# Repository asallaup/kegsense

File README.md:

# Sallaup KegSense

Keg weight/level monitoring for a keezer, by **Sallaup Electronics**.

Each keg sits on a load cell. A per-keg board reads the weight and sends
it over a wired connection to a central unit, which streams each keg's
brew name + weight out to a small OLED mounted right at that keg's own
tap (its own tiny MCU drives the display, right where you're pouring
from) and mirrors the same view to a web dashboard you can check
remotely — so you know how much beer is left without opening the lid.

## System overview

```
 Keg 1  --RJ11-->  |                |
 Keg 2  --RJ11-->  |     KegHub     |  --RJ45-->  KegStation
 Keg 3  --RJ11-->  |   (passive     |             (Raspberry Pi,
 Keg 4  --RJ11-->  |    wiring      |              web dashboard)
 Keg 5  --RJ11-->  |    panel)      |                   |
                    |                |                   v
                                              KegDisplay chain (OLED +
                                              Trinket M0 per tap, daisy-
                                              chained tap to tap)
```

Each keg's board is a **KegSensor** module (HX711 + 4 half-bridge strain
gauge sensors + RJ11 out). No Wi-Fi or radio anywhere inside or on the
keezer itself — everything in there is wired; KegStation, which sits
outside the keezer, is the only part with Wi-Fi (for the dashboard).

## Status

- 🚧 **KegSensor** (per-keg module) — **draft design**, still likely to
  change. Schematic + PCB routed and DRC-clean, 3D-printable case
  designed and validated, fab-ready Gerbers generated — but none of it
  has been physically built, and it hasn't been ordered/printed yet.
  Treat as a working draft, not a locked design, until it's been through
  a real build.
- 🚧 **KegHub** (in-keezer passive wiring panel) — wiring design
  (RJ11/RJ45 pin conventions, parts list) documented; physical build not
  started.
- 🚧 **KegStation** (central unit) — architecture decisions documented
  (platform, Wi-Fi provisioning, update mechanism, KegSensor-interfacing
  daemon language); no hardware or software built yet.
- 🚧 **Keg platform** (load cell mounting) — one part done: a derived,
  validated OpenSCAD load cell holder. Top/bottom mounting plates around
  it not designed yet.

## Repo layout

- [`hardware/kegsensor/`](hardware/kegsensor/) — KegSensor: per-keg
  sensor wiring (RJ11 pin conventions, parts list), KiCad schematic/PCB
  project, 3D-printable case (OpenSCAD), fab-ready Gerbers, and the load
  cell platform holder. See its own README(s) for details, known
  assumptions to verify against real hardware, and how to regenerate
  everything.
- [`hardware/keghub/`](hardware/keghub/) — KegHub: the in-keezer passive
  wiring panel design (RJ45 pin conventions, parts list, bench-test
  checklist).
- [`hardware/kegstation/`](hardware/kegstation/) — KegStation (central
  unit) planning doc: decisions made so far and what's still open.
- [`hardware/kegdisplay/`](hardware/kegdisplay/) — KegDisplay (per-keg
  tap indicator) planning doc: a small OLED + its own Trinket M0 MCU per
  tap, daisy-chained back to KegStation, each tap showing its own keg's
  brew name + weight directly.

## Before ordering/building anything

Both `hardware/kegsensor/README.md` and `hardware/kegsensor/wiring.md`
flag specific assumptions (HX711 module pin order, sensor diagonal
wiring) that need confirming against the actual parts once they're in
hand — cheap to fix now, annoying after boards are fabricated.

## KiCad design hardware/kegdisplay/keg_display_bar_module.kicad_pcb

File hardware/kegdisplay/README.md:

# KegDisplay — Sallaup Electronics

Part of the **Sallaup KegSense** keg-monitoring system, made by
**Sallaup Electronics**.

**KegDisplay** is the per-keg status indicator: a vertical WS2812 LED
bar in its own enclosure, mounted on the collar's side at each tap,
showing that keg's remaining % as a fill-level bar (more LEDs lit from
the bottom = more left — same read as a fuel gauge). No per-tap MCU —
**KegStation** (the central Raspberry Pi — see
[`../kegstation/`](../kegstation/)) drives the whole chain directly.
An off-the-shelf WS2812 strip is glued or screwed to the front of a
small custom PCB inside the enclosure, which gives it a rigid mount and
carries both chain connectors (see the revision note below for how this
settled). Brew-name display is a separate, experimental add-on — see
[`../kegtag/`](../kegtag/).

This is a planning doc — no hardware or software has been built yet.
Captures decisions made so far so they aren't lost before implementation
starts (see [`../kegsensor/wiring.md`](../kegsensor/wiring.md) and
[`../keghub/README.md`](../keghub/README.md) for the equivalent docs
that preceded the KegSensor module).

**Revision note**: this design has gone through several full rewrites,
kept in git history rather than deleted outright:
1. Originally an Arduino Nano + MAX485 board per tap, daisy-chained over
   RS-485 with a custom chain-position auto-addressing scheme.
2. Then a bare OLED module per tap wired star-topology through a
   TCA9548A I2C multiplexer at KegStation, dropping the Nano entirely.
3. Then, realizing an OLED at every tap was itself more display than the
   job needed, the per-tap hardware shrank further to just a status LED
   + a pushbutton, with the actual detailed information (brew name,
   weight) moved to a screen at KegStation instead.
4. **This version**: brings the OLED back, but on a much smaller MCU
   with its own onboard I2C - each tap's OLED shows its own brew name +
   weight directly, all the time, no button/KegStation-touchscreen
   detail view needed. The Nano-sized objection that killed revision 1
   doesn't apply this time; the shared-I2C-address conflict that killed
   the mux approach in revision 2 doesn't apply either (each tap's OLED
   is on its *own* MCU's I2C bus, not a bus shared across taps). The MCU
   choice within this revision itself went through several rounds:
   Adafruit Trinket M0 (real hardware I2C, easy USB/Arduino flashing,
   but ~$5-6/unit) -> Seeeduino XIAO SAMD21 (same capability, smaller
   board, similar cost) -> ATtiny10 (tiny and ~$0.30, but no hardware
   I2C/UART and needs a TPI programmer) -> CH32V003 (cheapest of all,
   ~$0.10-0.15, real hardware I2C, but RISC-V + WCH-LinkE is a bigger
   toolchain departure than anything else in this project) ->
   **ATtiny1614 in SOIC-14**, the settled choice: real hardware I2C,
   16KB flash/2KB RAM (enough for real OLED text, unlike ATtiny10's
   1KB), ~$0.60-1.20/unit (far cheaper than Trinket M0/XIAO, only a
   modest premium over CH32V003), programmed over UPDI (simpler than
   ATtiny10's TPI - a USB-serial adapter + one resistor is enough), and
   SOIC-14 is still hand-solderable (unlike QFN packages, which need
   reflow/hot air).
5. **This version**: dropped the OLED+MCU entirely. The real physical
   constraints at the mounting location (~100mm between taps, ~30mm max
   height) kept defeating every attempt to fit the ATtiny1614+OLED+
   connector assembly — landscape reorientation, connector swaps
   (KK-254 vs RJ14 vs audio jack), aggressive layout compaction all hit
   walls, most fundamentally that any locking/panel-mount connector's
   physical plug needs ~12-20mm of depth, which doesn't fit in the
   ~12mm gap left between taps once a board of any reasonable size is
   in place. Back to a WS2812 LED chain (first explored in revision 3),
   but as a 10-LED bar graph per tap instead of a single status LED,
   and with KegStation driving the chain directly — no per-tap
   MCU/logic at all, sidestepping the space problem instead of
   continuing to fight it.
6. **This version**: switched from a horizontal custom-PCB LED bar to a
   **vertical off-the-shelf WS2812B LED strip** mounted on the collar's
   side (~50mm width x ~130mm height available there - a much bigger
   budget than the ~100x30mm the horizontal layout was fighting for).
   Two wins at once: (1) a commercial strip at 140-200 LEDs/m gives
   18-26 LEDs over that length, cut to whatever length is wanted, so
   there's no custom PCB to design/fab at all - just a cut strip with a
   few wires soldered on at each end; (2) a vertical fill-level bar
   reads more intuitively than a horizontal one (same mental model as a
   fuel gauge or thermometer).
7. **This version**: brought a custom PCB back after all — not because
   the vertical layout was wrong, but to solve two things a bare
   commercial strip couldn't: a rigid mounting surface inside the box,
   and a way to get *both* chain connectors onto the box's bottom edge
   (see "connectors on left/right" below — both need to end up at the
   bottom, and a floppy 3-wire strip has no natural way to route a
   return path back down). Individual WS2812B LEDs are placed directly
   on a 2-layer PCB instead: front layer carries the LED chain bottom to
   top; after the top LED, a via drops the single DATA_OUT signal to the
   back layer, which routes it back down to the bottom-right connector.
   VCC/GND don't need this detour — they're shared rails running the
   full board height on the front layer, tapped directly by both
   connectors.
8. **This version**: swapped the 23 individually-placed LED footprints
   for an off-the-shelf WS2812 strip, glued or screwed to the front of
   the custom PCB. The PCB still solves the same two problems revision 7
   introduced it for (rigid mounting surface, both connectors on the
   bottom edge) — that didn't change. What changed: hand-laying out 23
   LED footprints/nets was more work than buying an assembled strip and
   mounting it. The PCB's job shrinks to rigid backer + both connectors
   + a soldered-wire path (the strip's own DIN/DOUT leads soldered to
   pads) instead of continuous copper running through 23 LED footprints.
   Nothing below reflects revision 7's individual-LED approach.

## Decisions so far

- **Per tap: an off-the-shelf WS2812 LED strip, glued or screwed to the
  front of a custom 2-layer PCB**, mounted vertically inside an
  enclosure on the collar's side. No per-tap MCU — KegStation lights
  however many LEDs correspond to the keg's remaining % as a bottom-up
  fill bar. Same chain-position addressing as every earlier revision —
  purely protocol-level, no firmware/logic at the tap.
- **Topology: daisy chain, 3 conductors (+5V, GND, WS2812 data)**,
  same as every earlier revision.
- **Power: 5V**, matching the Pi's logic level, same as every earlier
  revision — but sourced from its own dedicated supply injected into
  the chain, not drawn through the Pi itself (see
  [`../kegstation/README.md`](../kegstation/README.md) for why: LED
  current draw exceeds what the Pi's own PSU/GPIO can safely provide).
- **Mounting location: collar's right side, vertical**, not the tap
  face — ~50mm width x ~130mm height available there. Confirmed against
  the real keezer, not guessed: tap spacing ~10cm apart horizontally
  (real photo, 5 taps through a single wood plank, plus a direct
  measurement), collar board height 13cm (matches the ~130mm figure
  almost exactly), and the board is confirmed finished wood (despite
  looking unfinished in the photo) — the earlier reasoning against
  drilling a blind bore for cable routing (a visible mistake in
  installed, finished wood, with no way to redo it) holds as originally
  reasoned. Board thickness is the only dimension still unmeasured (see
  Still Open).
- **Housed in a rectangular enclosure** — protects the PCB and gives the
  LEDs a diffuser window instead of exposed dots. Box footprint sized to
  the ~50x130mm mounting budget above.
- **Both connectors live on the box's bottom edge, one on the left, one
  on the right, each with a short wire pigtail to the next tap's box** —
  not top/bottom of the box, even though the PCB inside runs vertically.
  Taps sit ~10cm apart *horizontally* along the collar, so the
  daisy-chain cable between one tap's box and the next needs to run
  sideways; bottom-left/bottom-right connector placement matches that
  real cable path instead of forcing an awkward top-to-bottom-then-across
  route.
- **PCB signal routing**: left connector (chain in) feeds pads at the
  strip's bottom (DIN) end via soldered wire leads. The strip itself
  carries data up its own length front-side; its DOUT lead at the top
  end solders to a pad, where a via drops DATA_OUT to the back layer,
  routing it straight back down to the right connector (chain out) —
  same detour concept as revision 7, now via a soldered wire+pad instead
  of continuous LED-to-LED copper. VCC/GND: the strip's own power leads
  solder to pads tied to shared rails on the front layer spanning the
  full board height, tapped directly by both connectors.
- **Mounting method (glue vs. screw) depends on which strip is
  sourced** — a flexible, adhesive-backed strip (the common type) only
  supports gluing; a rigid-PCB or aluminum-channel strip variant would
  support screws if one is sourced instead. Not decided (see Still
  Open).
- **PCB laid out and DRC-clean, board size settled: 34x132mm**, offset
  from the origin (x: 9.5-43.5mm, y: -2-130mm) — resized/shifted in the
  KiCad GUI from the original 50x130mm placeholder and confirmed as the
  right size. `generate_bar_schematic.py` / `generate_bar_pcb.py` in
  this directory build this board, kept in sync with that GUI edit.
  Which specific off-the-shelf strip to buy is still open (see Still
  Open) but must now fit this board size, not the other way around.
  J1/J2 still near the bottom, outward-
  facing (cable exits sideways), nudged off strict edge-flush/shared-Y
  placement in the GUI to clear each other's and MH2's courtyards after
  the resize. R1/C1 between them (unchanged). TP1-3 (strip's bottom
  GND/VCC/DIN leads) and TP4-6 (strip's top GND/VCC/DOUT leads) remain a
  tight 4mm-pitch cluster of hand-solder test points, replacing the 23
  LED footprints. Mounting holes MH1/MH2 both moved to the board's
  horizontal center in the GUI. ERC/DRC clean aside from known-benign
  warnings (`lib_footprint_mismatch` from UUID regeneration;
  `silk_over_copper` from the connectors' own default pin-1 silkscreen;
  `unconnected_items` since, like every earlier revision's generator
  script, this places components and assigns nets but does **not** emit
  copper traces/vias — it validates physical fit and clearance, not
  routing completeness; the DATA_OUT via + back-layer return trace is a
  routing detail for real layout, not modeled here).

## Superseded (revision 7, individual LEDs on PCB) — kept for reference

- **Per tap: 23x WS2812B-2020 (2.0x2.0mm) LEDs at 5mm pitch (200 LEDs/m)
  soldered directly onto the custom 2-layer PCB** — the smaller 2020
  package (vs. revision 5's 3.5x3.5mm Mini) gave comfortable clearance
  at this tight pitch. Superseded by revision 8's off-the-shelf strip
  glued/screwed to the same PCB — hand-laying out 23 individual LED
  footprints/nets was more generator-script work than buying an
  assembled strip; the PCB's role (rigid mount, both connectors on the
  bottom edge) carries forward unchanged.
- **PCB signal routing (individual-LED version)**: left connector fed
  the bottom LED's DIN directly; data climbed LED to LED on the front
  layer to the top LED's DOUT, where a via dropped DATA_OUT to the back
  layer, routed back down to the right connector. Same detour concept
  revision 8 keeps, just via continuous LED-to-LED copper instead of a
  strip's own leads soldered to pads.
- **PCB laid out and DRC-clean for this construction**:
  `generate_bar_schematic.py` / `generate_bar_pcb.py` in this directory
  build *this* (now superseded) board — 23 LEDs at 5mm pitch, board
  50x130mm, J1 bottom-left / J2 bottom-right both facing outward
  (JST-PH 3-pin horizontal, same footprint/angles as revision 5), R1/C1
  between them. ERC/DRC clean aside from known-benign warnings
  (`power_pin_not_driven` on VCC/GND — same accepted quirk as every
  earlier revision's schematic; `lib_footprint_mismatch` from UUID
  regeneration; `silk_over_copper` from the connectors' own default
  pin-1 silkscreen crossing their own pads). **Not yet regenerated for
  revision 8** — these scripts still model the individual-LED
  construction, not the strip-on-backer-PCB one (see Still Open).

## Superseded (revision 6, off-the-shelf strip) — kept for reference

- **Per tap: a commercial WS2812B LED strip (140-200 LEDs/m), cut to
  length.** No custom PCB. Superseded by revision 7's custom PCB, needed
  to give the strip a rigid mounting surface and to route a return path
  to both bottom connectors (see revision note above) — otherwise the
  core idea (vertical fill bar, ~50x130mm collar-side mounting, no
  per-tap MCU) carries forward unchanged.
- **Topology detail specific to a cut strip**: 3 pads at each end, a
  short pigtail soldered on at each end carrying them to a chain
  connector. Moot once LEDs are placed directly on a PCB instead.

## Superseded (revision 5, custom PCB LED bar) — kept for reference

The horizontal custom-PCB version (generate_schematic.py/generate_pcb.py
in this directory) went through extensive layout work — 10 LEDs down to
5, connector swaps, edge-flush J1/J2 for case-wall cutout access — all
now moot since revision 6 uses a cut length of commercial strip instead
of a custom board. Kept as-is in this directory rather than deleted;
treat as historical, not a current target to keep building against.

## Superseded (revision 4, ATtiny1614+OLED) — kept for reference

- **Per tap: one ATtiny1614 (SOIC-14) + one 0.91" SSD1306 I2C OLED.** The
  ATtiny1614 is its own I2C master for its own OLED — no shared bus, no
  address conflict, no mux (that was revision 2's problem, and it simply
  doesn't arise here since each tap's I2C bus is private to that tap).
  No button, no resistor ladder, no KegStation-side ADC — the OLED just
  always shows its own keg's brew name + weight. See the revision note
  above for the full MCU comparison (Trinket M0/XIAO/ATtiny10/CH32V003)
  that led here.
- **Development workflow: Arduino IDE + megaTinyCore, prototype on a
  SOIC-to-DIP adapter, flash over UPDI, keep a UPDI header on the final
  board.** Concretely:
  1. Write firmware as a normal Arduino sketch (megaTinyCore adds
     ATtiny1614 as a board option, `Wire.h` works for I2C).
  2. Prototype on a breadboard by soldering the chip onto a cheap
     SOIC-14-to-DIP adapter board first, rather than committing straight
     to a custom PCB.
  3. Flash via **SerialUPDI** — a plain USB-to-serial adapter plus one
     resistor between its TX/RX lines, wired to the chip's UPDI pin.
     megaTinyCore supports this directly as an Arduino IDE upload
     method, so it's still just "hit Upload."
  4. Once firmware is solid, solder a chip onto the real per-tap PCB,
     which includes its own **3-pin UPDI header (UPDI/VCC/GND)** so it
     can be reflashed in place later (fixing a bug or tweaking the OLED
     layout after it's already mounted at the tap) without desoldering.
  5. **Field reflashing: temporary cable from KegStation's own UART pins
     to J4, one tap at a time** — a Pi's UART (TX/RX) can run SerialUPDI
     directly, so KegStation itself is the programmer, no separate
     laptop/USB adapter needed. Not a permanent connection (UPDI is
     point-to-point; it can't ride the shared chain bus without hitting
     every tap's chip at once) — walk up to the tap, plug in, flash,
     unplug. J4 stays inside the case (no dedicated access port needed
     in the lid/body — see Still Open) since this is infrequent enough
     that opening the case is an acceptable cost.
  6. **Possible future upgrade, not implemented now**: a bootloader that
     receives firmware over the chain itself (via J1, reusing the same
     "consume my chunk, relay the rest" addressing idea as the brew-data
     relay), removing the need to physically visit a tap at all for
     routine updates. J4/UPDI would still be needed for a blank chip's
     very first flash either way. Deliberately deferred — not worth the
     bootloader complexity until the rest of the system is proven out.
- **Chain addressing: still positional, like the WS2812 version, but now
  relayed by firmware instead of being protocol-free.** KegStation
  streams all 5 kegs' data down the chain in tap order; each ATtiny1614
  reads its own chunk off its "chain in" pin (a bit-banged serial RX),
  keeps that chunk for its own OLED, and relays everything after it out
  its "chain out" pin (bit-banged serial TX) to the next tap. No
  per-tap address to configure, same principle as the LED chain, just
  carrying real data (text) instead of raw color bits.
  - **Pin budget**: ATtiny1614 (SOIC-14) has 14 pins total: VDD, GND,
    UPDI (shared with reset, freed up by the UPDI header above), and 11
    GPIO. 2 go to hardware I2C (SDA/SCL, to the OLED), 2 to chain
    in/chain out, leaving several spare — a much more comfortable
    budget than Trinket M0's 5 broken-out GPIO.
- **Topology: daisy chain**, one cable hopping tap to tap, same as the
  WS2812 version and for the same reason — the chain-position addressing
  scheme requires it.
  - **3 conductors used: +5V, GND, chain data** (one direction only —
    KegStation "down" through the chain; no need for a return path,
    since each tap only needs to receive, not report back). 2 jacks per
    tap (IN from upstream, OUT to downstream), **Molex KK-254 (4-pin,
    2.54mm pitch)** — not RJ14 like KegSensor's jack, switched for board
    size (KK-254's courtyard is ~1/3 RJ14's) while keeping a real
    locking latch, unlike JST-PH (used only for the short internal OLED
    cable, where no latch is needed). 4th contact left unused/spare.
  - **Same known IN/OUT-swap fragility as the WS2812 version, re-accepted
    for the same reason**: chain-in and chain-out are different pins on
    the Trinket, not symmetric, so a swapped cable breaks that tap and
    everything downstream of it. Worth keying/labeling the jacks clearly
    at install time.
  - **Chain fragility**: a disconnected or dead tap breaks every tap
    downstream of it, same as any physical daisy chain — already
    discussed and accepted in the WS2812 revision, still true here.
- **Power: 5V** on the shared rail, matching the Pi's own 5V — the OLED
  module runs fine off 5V directly (most SSD1306 breakouts have their
  own onboard 3.3V regulator). ATtiny1614's own VDD range/regulation
  need still needs confirming (see Still Open) - it may need a small
  local 3.3V regulator on the per-tap board, unlike Trinket M0 which
  handled that internally.
- **OLED-to-board cable: 4-pin JST-PH (2mm pitch).** The lid-to-body run
  is under 2cm, short enough that a compact connector fits better than
  a pin header — hand-solderable, unlike the finer 1mm-pitch JST-SH
  alternative.
- **Mounting location: outside the keezer** — the OLED/ATtiny1614
  assembly sits on the tap's own exterior face, same reasoning as every
  earlier revision: no part of the wiring needs to enter the cold zone.
- **Mechanical split: main board inside the case body, OLED mounted on
  the case lid, connected between them by a short wire harness** (not a
  single rigid board carrying both) - decided when starting the case/lid
  design, still in progress (see Still Open). The OLED's 4-pin header
  (VCC/GND/SCL/SDA) on the main board is exactly this cable's connection
  point, not a directly-soldered display.
- **Physical cable routing: hidden along the collar's exterior, under a
  paintable plastic cord cover** — not routed through the collar's
  interior cavity (both ends are already outside, so dipping into the
  cold zone would be pure downside), and not bored through the solid
  wood either (the collar here is already built and finished — a long
  blind bore through installed wood risks a visible drilling mistake
  with no way to redo it, unlike drilling before assembly). Cable runs
  along an inconspicuous exterior seam (e.g. where the collar meets the
  freezer body) and is covered by an off-the-shelf paintable plastic
  cord cover, painted to match — reads as a deliberate trim detail
  instead of an exposed wire.
- **Not yet built or prototyped** — this whole design came out of
  conversation, not a physical test yet. Same "verify against real
  hardware before calling it done" standard as everything else in this
  project.

## Still open

- **Which off-the-shelf strip to source** — not chosen. Board size
  (34x132mm) is now settled, so this is a fit-to-board search, not an
  open-ended one: needs a strip whose usable length fits the ~132mm
  board height, with end-lead spacing compatible with the TP1-3/TP4-6
  hand-solder clusters (revisit their exact positions in
  `generate_bar_pcb.py` once a strip is picked, if its real lead spacing
  differs from the current placeholder). Also determines whether glue or
  screws are possible (see "Mounting method" above — needs a rigid-PCB
  or aluminum-channel strip for screw-mounting; a standard flexible
  adhesive-backed strip only glues).
- **Enclosure: first-draft 3D-printable case modeled, NOT verified
  against real hardware yet.** `case_bar.scad` /
  `generate_case_bar.sh` (this directory) build two parts: `base`
  (solid wall — no window, side walls with left/right cutouts for
  J1/J2's cable exit, two PCB standoff posts at MH1/MH2, four corner
  posts for the lid, two mounting flanges on its top/bottom edges with
  wood-screw clearance holes) and `lid` (a frame with the diffuser
  window cut through it over the strip's span, four screw holes to
  close onto the base's corner posts). **The base, not the lid, is the
  face that mounts to the collar** — the lid carries the window and
  must face outward into the room for the LEDs to actually be visible;
  mounting the lid flush against the collar would hide them against the
  wood. Outer footprint ~43x141mm
  (board 34x132mm + margin + wall), depth ~15mm (component/strip
  clearance + board + standoff). Renders cleanly (`openscad`, both
  parts report `Simple: yes`) — see `case_bar_base_preview.png` /
  `case_bar_lid_preview.png`. Component clearance depths (JST-PH body
  height, strip thickness) are typical values, not measured off real
  parts — same "verify before calling it done" standard as the rest of
  this project; don't print for real without checking against actual
  hardware first. Diffuser window material/fit itself is still
  unaddressed (just an open cutout right now, no diffuser panel
  modeled). Two-point standoff mounting (not four-corner) may need a
  card-edge rail added later if the board flexes over its 132mm length
  in practice.
- **Collar board's thickness** — not measured (height 13cm and finished
  status are now confirmed, see above).
- **Wire gauge for the pigtails** at J1/J2 — not decided.
- **Reverse-polarity protection** — not reconsidered for this revision.
- **KegStation's own side**: the code that computes each keg's % and
  drives the WS2812 chain — not written yet. Brew-name/level display
  (ESL hub, tag protocol) is tracked separately, see
  [`../kegtag/`](../kegtag/).
- `case.scad`, the lid board (`keg_display_lid_module`), the ATtiny1614
  main board's KiCad files, and the revision-5 LED-bar KiCad files
  (`generate_schematic.py`/`generate_pcb.py` in this directory) are all
  obsolete — kept in git history, not deleted.

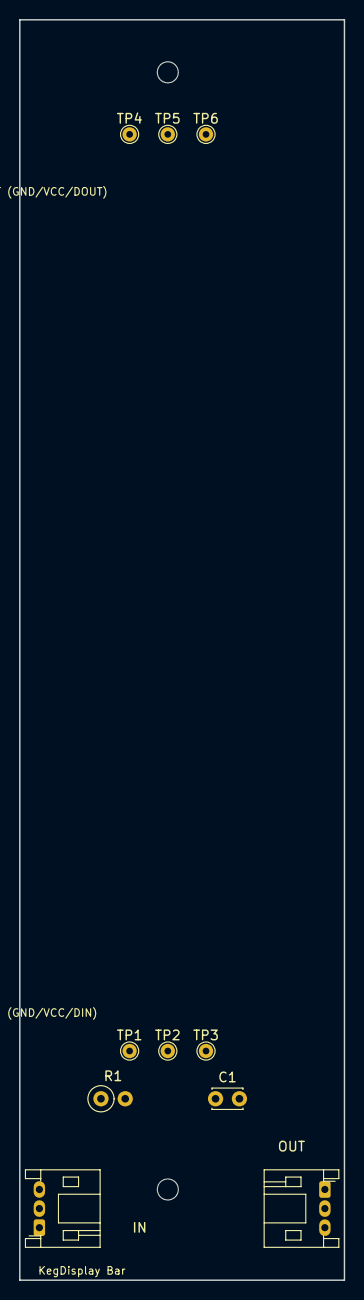
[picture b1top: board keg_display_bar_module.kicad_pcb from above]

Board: 2 copper layers, 34.0 x 132.0 mm, 12 parts (0 on the bottom side), 5 nets, no tracks yet.

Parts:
C1: C_Disc_D3.0mm_W2.0mm_P2.50mm
J1, J2: JST_PH_S3B-PH-K_1x03_P2.00mm_Horizontal
MH1, MH2: MountingHole_2.2mm_M2
R1: R_Axial_DIN0207_L6.3mm_D2.5mm_P2.54mm_Vertical
TP1, TP2, TP3, TP4, TP5, TP6: TestPoint_THTPad_D1.5mm_Drill0.7mm

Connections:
DATA_0: J1.3, R1.1
DATA_1: R1.2, TP3.1
DATA_OUT: J2.3, TP6.1
GND: C1.2, J1.1, J2.1, TP1.1, TP4.1
VCC: C1.1, J1.2, J2.2, TP2.1, TP5.1

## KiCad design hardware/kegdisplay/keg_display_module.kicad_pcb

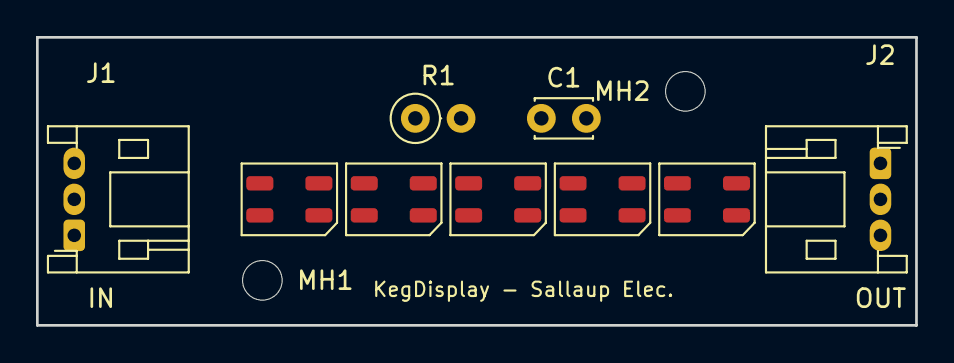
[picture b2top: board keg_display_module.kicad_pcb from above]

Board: 2 copper layers, 48.8 x 16.0 mm, 11 parts (0 on the bottom side), 9 nets, no tracks yet.

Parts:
C1: C_Disc_D3.0mm_W2.0mm_P2.50mm
J1, J2: JST_PH_S3B-PH-K_1x03_P2.00mm_Horizontal
LED1, LED2, LED3, LED4, LED5: LED_WS2812B-Mini_PLCC4_3.5x3.5mm
MH1, MH2: MountingHole_2.2mm_M2
R1: R_Axial_DIN0207_L6.3mm_D2.5mm_P2.54mm_Vertical

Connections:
DATA_0: J1.3, R1.1
DATA_1: LED1.4, R1.2
DATA_2: LED1.2, LED2.4
DATA_3: LED2.2, LED3.4
DATA_4: LED3.2, LED4.4
DATA_5: LED4.2, LED5.4
DATA_6: J2.3, LED5.2
GND: C1.2, J1.1, J2.1, LED1.3, LED2.3, LED3.3, LED4.3, LED5.3
VCC: C1.1, J1.2, J2.2, LED1.1, LED2.1, LED3.1, LED4.1, LED5.1

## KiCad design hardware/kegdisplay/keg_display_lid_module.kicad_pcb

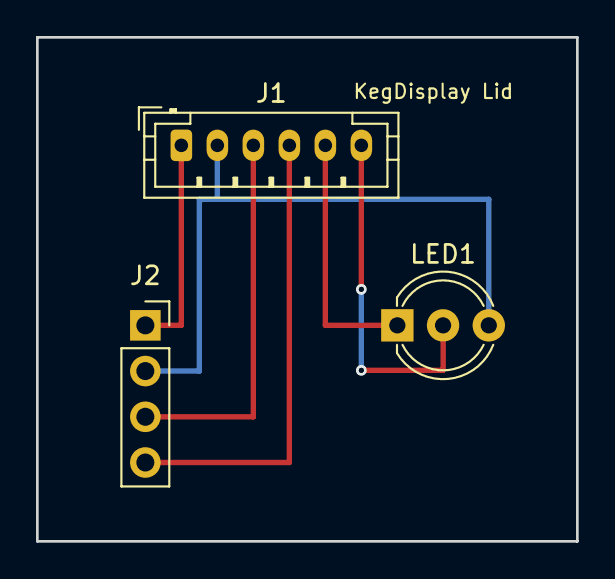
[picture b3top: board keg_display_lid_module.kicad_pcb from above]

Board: 2 copper layers, 30.0 x 28.0 mm, 3 parts (0 on the bottom side), 6 nets.

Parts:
J1: JST_PH_B6B-PH-K_1x06_P2.00mm_Vertical
J2: PinSocket_1x04_P2.54mm_Vertical
LED1: LED_D5.0mm-3

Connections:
GND: J1.2, J2.2, LED1.3
GREEN_LED: J1.6, LED1.2
SCL: J1.3, J2.3
SDA: J1.4, J2.4
VCC: J1.1, J2.1
YELLOW_LED: J1.5, LED1.1

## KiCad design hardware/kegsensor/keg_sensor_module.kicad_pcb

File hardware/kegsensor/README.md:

# KegSensor — Sallaup Electronics

Part of the **Sallaup KegSense** keg-monitoring system, made by
**Sallaup Electronics**.

**KegSensor** is the per-keg carrier board: hosts the HX711 breakout
module, terminates the 4 half-bridge sensor leads (bussed/paired per
`wiring.md`), and exits to the in-keezer hub over RJ11. One board
per keg.

KiCad 9 project. Both schematic and PCB (footprints placed, fully routed,
2-layer) are done and validated (see Validation below).

## Fabrication

**Send `KegSensor_RevA_gerbers.zip` to the PCB manufacturer.** That's the
complete, standard deliverable — a fab house doesn't need the `.kicad_pcb`
file itself (though most modern ones, e.g. JLCPCB/PCBWay, also accept it
directly if you'd rather skip the export step). It contains, generated via
`kicad-cli pcb export gerbers`/`export drill`:

| File | Contents |
|------|----------|
| `*-F_Cu.gtl` / `*-B_Cu.gbl` | Copper layers (top/bottom) |
| `*-F_Mask.gts` / `*-B_Mask.gbs` | Soldermask |
| `*-F_Silkscreen.gto` / `*-B_Silkscreen.gbo` | Silkscreen (incl. the KegSensor/Rev A branding) |
| `*-F_Paste.gtp` / `*-B_Paste.gbp` | Solder paste stencil (only matters if you're getting a stencil cut too) |
| `*-Edge_Cuts.gm1` | Board outline |
| `*-job.gbrjob` | Gerber job file (metadata some fabs use to auto-detect stackup) |
| `*-PTH.drl` / `*-NPTH.drl` | Drill files — plated (component holes) and non-plated (J7's 2 mounting bosses) separately |

The individual files are also in `fab/` (not zipped) if a fab's upload
tool wants them one at a time rather than as an archive, along with
`*-drl_map.pdf` drill maps (human-readable cross-reference of hole
sizes/positions — not needed by the fab, just useful if you want to
sanity-check the drill file yourself).

**Order quantity**: 5 (one per keg) — check the fab's pricing breaks
first, since many charge nearly the same for 5 as for 10.

**Before ordering**: resolve the two items under Known assumptions below
(J6 pin order, SIG_POS/SIG_NEG diagonal pairing) if you haven't already —
both require rerouting, which is easy to do before fabrication and
annoying after.

Regenerate the fab package after any board changes:
```
kicad-cli pcb export gerbers --layers "F.Cu,B.Cu,F.Paste,B.Paste,F.SilkS,B.SilkS,F.Mask,B.Mask,Edge.Cuts" -o fab/ keg_sensor_module.kicad_pcb
kicad-cli pcb export drill --format excellon --excellon-separate-th --excellon-units mm --generate-map --map-format pdf -o fab/ keg_sensor_module.kicad_pcb
```

## Files

- `keg_sensor_module.kicad_pro` — project file, open this in KiCad
- `keg_sensor_module.kicad_sch` — schematic (see `keg_sensor_module.pdf` for
  a quick look without opening KiCad)
- `keg_sensor_module.kicad_pcb` — routed board, 155×90mm outline, 4× M3
  clearance mounting holes at the corners (6,6)/(150,6)/(6,84)/(150,84)
  board-local (see `keg_sensor_module_top.png` / `_bottom.png` for a quick
  look, or `keg_sensor_module_3d.png` for an isometric render with real
  component shapes)
- `case.scad`, `case_base.stl`, `case_lid.stl` — 3D-printable enclosure,
  see Case below
- `generate_schematic.py` / `generate_pcb.py` — the scripts that generated
  the two files above. If a pin-order assumption turns out wrong once you
  have the real hardware in hand (see Known assumptions below), fix it in
  the script and rerun rather than hand-editing the `.kicad_sch`/`.kicad_pcb`
  text. Requires `pip install sexpdata` and a local KiCad 9 install (the
  scripts read symbol/footprint definitions straight out of
  `/Applications/KiCad/KiCad.app/Contents/SharedSupport/`).
  **If you have this project open in KiCad while regenerating, close and
  reopen the PCB editor afterward** — the scripts overwrite the file on
  disk directly, which KiCad won't pick up in an already-open editor.

## Connectors

| Ref | Part | Pins |
|-----|------|------|
| J1 | Screw terminal, sensor "FL" corner | 1=E+ (Red) 2=E- (Black) 3=Signal (White) |
| J2 | Screw terminal, sensor "FR" corner | 1=E+ (Red) 2=E- (Black) 3=Signal (White) |
| J3 | Screw terminal, sensor "BR" corner | 1=E+ (Red) 2=E- (Black) 3=Signal (White) |
| J4 | Screw terminal, sensor "BL" corner | 1=E+ (Red) 2=E- (Black) 3=Signal (White) |
| J5 | Female header, HX711 load-cell side | 1=E+ 2=E- 3=A+ 4=A- |
| J6 | Female header, HX711 digital/power side | 1=GND 2=DT 3=SCK 4=VCC |
| J7 | RJ11 jack to hub (RJ14 6P4C) | 1=GND 2=VCC 3=SCK 4=DT |

Nets: `EXC_POS`/`EXC_NEG` bus J1–J4 pin1/pin2 into J5; `SIG_POS` ties
J1+J3's signal leads (diagonal) into J5.A+, `SIG_NEG` ties J2+J4's into
J5.A-; J6↔J7 pass GND/DT/SCK/VCC straight through to the hub cable.

## Known assumptions to confirm against real hardware

- **J6 pin order (GND,DT,SCK,VCC)** is a common layout for these HX711
  breakouts but varies by manufacturer — check your module's silkscreen
  before soldering the header, fix in `generate_schematic.py` if different.
- **Diagonal pairing (J1+J3→SIG_POS, J2+J4→SIG_NEG)** depends on which
  corner each sensor physically sits at and its mounting orientation —
  follow the kit's included wiring diagram; if the reading comes out
  inverted or dead-flat, swap the SIG_POS/SIG_NEG pairing.
- **J7 uses KiCad's stock RJ14 (Connfly DS1133-S4) footprint** — a genuine
  6P4C connector (6-position body, 4 contacts), which is mechanically what
  "RJ11" means in practice for a 4-wire line cord (RJ9, used in an earlier
  draft of this board, is a different 4P4C body meant for phone handset
  cords, not line cords — swapped out after review). Still worth checking
  the exact part you buy against this footprint's dimensions before
  ordering the board, since real-world RJ11 jacks vary in body/pin
  spacing between manufacturers.

## Pending design change (decided, not yet applied to the KiCad files)

- **J1-J4 switching from `TerminalBlock_bornier-3_P5.08mm` to
  `TerminalBlock_Phoenix_PT-1,5-3-3.5-H_1x03_P3.50mm_Horizontal`** —
  3.5mm pitch instead of 5.08mm, to shrink the board. Checked two 3.5mm
  candidates before picking, since pitch alone doesn't guarantee a
  smaller footprint: WAGO 2601-1103 (3.5mm pitch, but 13×15.5mm
  courtyard — *taller* than the current part, would make the board
  worse in the already-tight Y direction) vs. **Phoenix
  PT-1,5-3-3.5-H** (3.5mm pitch, 11.5×8.6mm courtyard — narrower than
  the current 15.6×8mm, same horizontal thin-profile mounting style).
  Phoenix is the one to use.
  - **Not yet applied** — `generate_schematic.py` (footprint string +
    `PIN_DX` pin spacing, currently tuned for 5.08mm) and
    `generate_pcb.py` (J1-J4 placement/routing, extensively DRC-iterated
    around the current footprint's exact pad positions — see Routing
    below) both need rework, not just a footprint-string swap.
  - **Deliberately deferred to Phase 6** of `IMPLEMENTATION_PLAN.md` —
    the first prototype is being hand-wired on perfboard, not the
    custom PCB, so this change isn't blocking anything yet. Apply it
    once Phase 5 passes and the real PCB actually gets ordered.

## Physical layout

Sensor terminals (J1–J4) sit in a horizontal row close to the board's top
edge (y≈10, 30mm pitch), ordered FL/BR/FR/BL left-to-right (not source
order) so the diagonal pairs (SIG_POS = J1+J3, SIG_NEG = J2+J4) sit next to
each other. Unrotated (angle=0, the library's default orientation) — an
earlier version rotated each part -90° to make the bus routing trivial
(every part's pins landing on their own single x instead of sharing a y
with every other part's pins), but that was a routing convenience, not a
requirement; unrotated works too, it just needs more deliberate lane/layer
routing (see below). J5 (HX711 load-cell side) sits below the row, on the
same side — these are the noise-sensitive analog connections, kept short
and away from the digital/power section. J6 (HX711 digital side) sits with
J5; J7 (RJ11 to hub) is rotated 180° and placed flush with the board's
*bottom* edge (y=90) — moved here from the right edge. Any edge-mounted
connector belongs at the board edge as a matter of course, independent of
the case (this board had a real bug once from *not* following that rule —
J7 originally sat mid-board with no edge access at all; see git history).

Each of J1-J4 has "R B W" silkscreened directly above its 3 pins, one
letter per pin, matching the sensor lead colors in the table above (Red
E+, Black E-, White Signal) — so wiring a sensor by color doesn't need
the README open next to the board. Fixed pin order (1=R, 2=B, 3=W) on
every connector regardless of which physical corner it's wired to.
Positioned in the gap between the board's top edge and each connector's
own body, clear of both the edge and each connector's reference
designator (checked via DRC's silk_overlap rule after placing it, not
just eyeballed).

J5 and J6 (the HX711 header pins) are labeled too — E+/E-/A+/A- and
GND/DT/SCK/VCC respectively, one per pin, matching the Connectors table
above. Both are `PinSocket_1x04_P2.54mm_Vertical`: a single column with
all 4 pins stacked in Y at one X (2.54mm pitch), unlike J1-J4's
horizontal row, so these labels go beside each pin rather than
above/below — there's no room between adjacent pins at that pitch for a
label. J5's sit on the left, J6's on the right (per explicit request —
opposite sides). J6's labels needed extra clearance from the footprint's
own outline (GND/SCK/VCC are 3 characters, wide enough at their first
position to clip it — DRC caught it, not eyeballing).

Routing uses both copper layers, extensively. With J1-J4 unrotated, every
one of their 12 pins (pin1/2/3 × 4 parts) sits at the exact same y=10 —
unlike the rotated layout, where each pin *number* got a fixed y shared by
all 4 parts (turning "pin N, every part" into one trivial straight bus),
here every net needs its own dedicated lane below the row plus vertical
drops from each of its own pins down to that lane, and since the 4 nets'
pin x-positions are interleaved across the same 20-110 span, a drop for a
"deeper" net's lane inevitably passes through a "shallower" net's lane at
some point along that span. EXC_POS and EXC_NEG (each needing the full row
width) are kept on separate copper layers entirely so crossing each other
in plan view isn't a short; SIG_POS/SIG_NEG only span half the row each,
but still have to get past *both* of those, so their drops explicitly hop
layers (via) at each crossing rather than relying on a single layer
choice. J7's move to the bottom edge similarly turned its own approach
into a small routing puzzle: GND and SCK's target pads are only 1.02mm
apart, so straight verticals into either one grazed the *other's*
neighbor pad (VCC) for their whole length — fixed with an offset
approach-and-jog into each pad's own y, and DT/SCK/GND's lanes had to be
depth-ordered (matching the order of their target x's) so a deeper lane's
horizontal run doesn't cross a shallower one's drop. Each net's initial
jog off of J6 goes east (toward J7), not west first — per explicit
request — which flips *which* net needs the shallowest lane: since every
lane then extends the rest of the way east to J7 regardless of where its
own stub sits, the depth/stub-position pairing that avoids crossings
turned out to be the mirror image of the west-jog version (shallowest
lane ↔ stub furthest from J6, not closest).

GND and SCK are each a single unbroken line on one layer (B.Cu and F.Cu
respectively), no vias — J6's pads are through-hole, so a track can just
start on whichever layer it needs directly at the pad; both had a
vestigial F.Cu stub in an earlier version that wasn't actually needed.
VCC_3V3 and DT can't drop theirs, though, and this isn't a missed
simplification — checked exhaustively, not just patched around the first
conflict DRC caught: VCC's own source row at J6 sits inside DT's drop's
depth range, and DT's row sits inside VCC's, so whichever one is "in the
way" at that crossing needs to be on the other layer right there. Two
vias is the minimum for this connector, not four.

See the comments in `generate_pcb.py` for the exact reasoning behind each
routing decision — several were only found by DRC catching a real short
or clearance violation, not worked out by eye in advance.

**Note on KiCad footprint rotation**: got this wrong once already — KiCad's
`(at x y angle)` rotation is the opposite sign of the standard math
convention (confirmed empirically by checking DRC's reported pad
coordinates against a hand-rotated prediction, the same way the schematic's
Y-axis quirk was caught earlier). J7 uses `angle=180` to point its cable
face toward +Y (the bottom edge); don't assume a given angle achieves a
given direction without checking actual reported pad/courtyard positions
first — that's what caught this, not reasoning from the formula alone.

## Next steps

1. Confirm the two assumptions above against your actual HX711 modules and
   kit wiring diagram; adjust and rerun `generate_schematic.py` (and
   `generate_pcb.py`, since its net assignments mirror the schematic's) if
   either turns out different.
2. Once you've bought the actual RJ11 jack, double-check its footprint
   against RJ14 (Connfly DS1133-S4) — if the pad spacing/count differs,
   swap it in `generate_pcb.py` and re-route just that connector's traces.
3. Add a ground pour on the analog section if you want extra noise
   margin (not done here — the board routes clean without one, but it's a
   cheap improvement for a load-cell signal).
4. Order 5 (one per keg).

## Case

`case.scad` is a parametric OpenSCAD design: an open-top base plus a
separate flat lid, screwed together at 4 corner posts (M3 self-tapping,
2.5mm pilot holes) — see `case_base_preview.png` / `case_base_preview_2.png`
/ `case_lid_preview.png` for renders.

- Sized around the board's actual footprint (155×90×1.6mm) with a 3mm gap
  to the inner walls and 2mm walls, so it should print fine on a standard
  FDM printer with no supports needed (lid is flat, base has no overhangs
  beyond straight vertical walls).
- The board sits on 4 short standoff posts (5mm, at the PCB's own mounting
  holes) held down by M3 screws from above; the lid attaches separately at
  the box's 4 corners, also M3.
- Component clearance above the board is a flat 15mm assumption (covers
  the tallest part here, the RJ14 jack, with margin) — I don't have exact
  height dimensions for any of these parts from datasheets, so treat this
  as a reasonable guess, not a verified fit. If a first print is too
  cramped, bump `component_clear` in `case.scad` and reprint just the base.
- **Front wall (y=0) has an open cutout** spanning the J1–J4 sensor
  terminal row, for the 4 sensor cables to exit (board-local y=0 is the
  board's own top edge, which sits against the case's front wall).
- **Back wall (y=outer_h) has a cutout matching J7's position** — moved
  here from a right-wall cutout when J7 moved from the board's right edge
  to its bottom edge (board-local y=90, which sits against the case's
  back wall — see Physical layout above). Earlier drafts had J7 positioned
  mid-board with a cutout nowhere near it — caught by directly computing
  J7's courtyard position against the case's wall coordinates rather than
  assuming the cutout was in the right place; fixed by moving J7 to the
  board edge (any case built around a mid-board position would need an
  internal tunnel to reach the connector, which isn't good practice
  regardless of the case).
- **Base is branded, engraved (not raised)**, both lines on the right
  wall (x=outer_w — the one wall without a connector cutout, now that
  J1-J4's cutout (front) and J7's (back) both claim one): "KegSensor"
  (bold, size 5) above "Sallaup Electronics" (italic, size 2.6, smaller as
  a subtitle). Recessed 0.6mm into the 2mm wall (1.4mm remains, plenty
  strong), centered horizontally and stacked vertically in the safe
  z-band shared with the connector cutouts. See
  `case_engrave_right_preview.png` — rendered as a true 2D orthographic
  projection from the wall's own outside-viewer perspective, not a 3D
  angle shot, because that's what actually caught a real bug the first
  time this branding was added (below). Text is generated with OpenSCAD's
  `text()` primitive directly from the strings in `case.scad`, not
  hand-drawn, so there's no typo risk — but getting an engraved letter
  *oriented* correctly on a vertical wall needs real verification, not
  assuming: the original front-wall attempt read upside-down at first; a
  fix reasoned from a 3D perspective render (a 180° rotation) corrected
  the vertical flip but introduced a horizontal mirror instead, only
  caught by switching to a true top-down 2D projection. `wall_text_right()`
  — a new module, following the same front/back pattern but re-derived
  from scratch for a wall on the other axis, not assumed by analogy —
  is what's in use now that branding moved to the right wall (freed up
  once J7's cutout claimed the back wall). Derived by tracking exactly
  what each OpenSCAD transform does to a known point rather than guessing,
  then verified the same way as before (a true 2D cross-section at the
  engrave depth, from the actual outside-viewer's perspective) — correct
  on the first attempt this time, though it was checked regardless rather
  than assumed correct from the derivation alone. `wall_text_front()` and
  `wall_text_back()` are both unused now but kept in case a wall needs
  text again later.

Regenerate with `./generate_case.sh` after editing `case.scad` (needs
OpenSCAD: `brew install --cask openscad`; this cask fails macOS Gatekeeper,
so also run `xattr -dr com.apple.quarantine "/Applications/OpenSCAD-2021.01.app"`
once after installing). Print at 0.2mm layers, 3+ perimeters, 20%+ infill;
PETG or ABS recommended over PLA since this lives inside a keezer at
fridge/freezer temperature and PLA gets brittle cold.

## Validation performed

- `kicad-cli sch erc` → 0 errors, 0 warnings
- `kicad-cli sch export netlist` → all 8 nets manually checked against the
  intended design (see table above)
- `kicad-cli sch export pdf` → visually reviewed, no overlapping labels or
  stray connections
- `kicad-cli pcb drc` on the fully routed board → 0 errors, 0 unconnected
  pads (only one pre-existing accepted warning remains: the
  local-footprint-override notice for J7's custom RJ14 footprint — see
  its own comment). Iterated repeatedly: the first full layout pass found
  17 real clearance/short issues from too-tight spacing; switching J7 from
  the RJ9 to the RJ14 footprint reset the J6↔J7 routing and took several
  more DRC-guided rounds to clear, since RJ14's pads are much more tightly
  packed. Moving J1-J4 to a horizontal row (see Physical layout) went
  through the same cycle: a straight diagonal tap point cut through an
  unrelated pad's copper twice before landing on the current routing, each
  time caught by DRC, not by eye. That pass also surfaced a separate
  latent bug: `generate_pcb.py`'s footprint copies kept the *library's*
  pad/graphic UUIDs verbatim, so multiple instances of the same footprint
  (J1/J3/J2/J4, all `TerminalBlock_bornier-3`) shared identical pad UUIDs
  - DRC started mislabeling which physical pad a violation was actually
  against once there were 4 copies on the board. Fixed by re-rolling every
  nested UUID per instance, not just the footprint's own top-level one.
- Un-rotating J1-J4 back to angle=0 and moving J7 to the bottom edge (a
  later request) meant redesigning essentially all of this board's
  routing again, and went through several more DRC-caught rounds: a
  diagonal from J1-J4's row to J5 cut through the SIG_POS lane;
  SIG_NEG's approach crossed straight through the J6↔J7 corridor's own
  drops; and J7's GND/SCK approaches (straight verticals into their own
  target x) each grazed the *other's* neighboring pad, since GND/SCK and
  VCC/DT sit only ~1mm apart in the tight RJ14 pad cluster. Each was a
  real `tracks_crossing`/`shorting_items`/`clearance` error, not a style
  preference — fixed with offset approach paths, layer hops, and
  depth-ordered lanes; see `generate_pcb.py`'s comments for the specifics.
- `kicad-cli pcb render` → top and bottom copper renders visually reviewed
  for sane, non-overlapping routing
- Case: OpenSCAD's CGAL export reports both `case_base.stl` and
  `case_lid.stl` as `Simple: yes` (valid, manifold, watertight solids —
  the check that predicts whether a slicer will handle a model cleanly).
  OpenSCAD's own GUI preview render didn't work headlessly in this
  environment (Gatekeeper/OpenGL context issue), so I rendered the actual
  exported STLs with a separate tool (matplotlib) from multiple angles
  and reviewed them for the checks that matter here: box walls intact
  where expected, both cutouts present at plausible positions, and the
  two post types (corner lid-posts vs. PCB standoffs) landing at distinct,
  non-colliding locations.
- J7-reachability fix: computed J7's courtyard bounding box in case-outer
  coordinates directly (not eyeballed) and checked it against the right
  wall cutout's coordinates before re-rendering, then re-rendered the
  updated STL and visually confirmed an actual opening lines up with the
  connector from two angles.
- Wall engraving: `case_base.stl` still reports `Simple: yes` after the
  text cutouts. Orientation specifically verified with true 2D orthographic
  projections of each wall (not 3D perspective renders, which is what
  produced a wrong first read) from that wall's actual outside-viewer
  angle — caught and fixed a vertical-flip bug and a horizontal-mirror
  bug this way before calling it done (see Case section above for the
  detail).

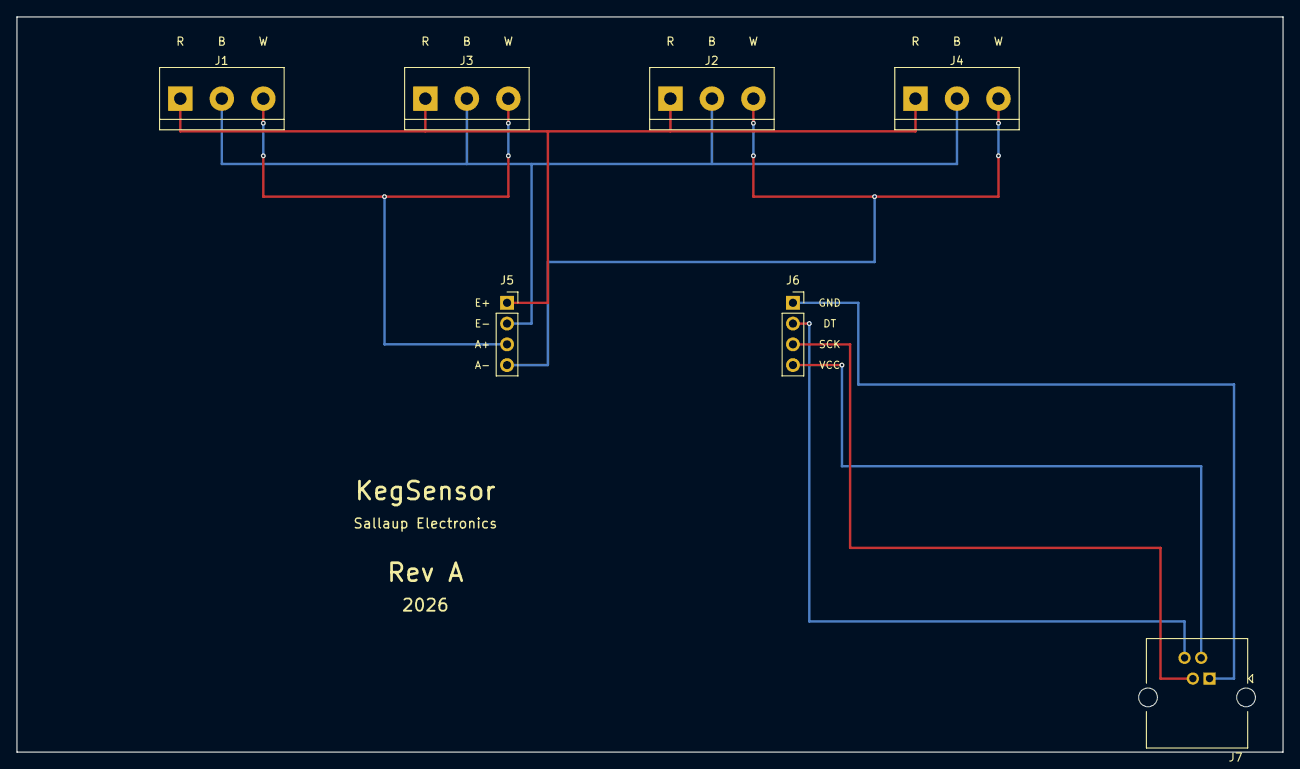
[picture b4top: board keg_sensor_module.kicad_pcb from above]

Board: 2 copper layers, 155.0 x 90.0 mm, 7 parts (0 on the bottom side), 8 nets.

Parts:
J1, J2, J3, J4: TerminalBlock_bornier-3_P5.08mm
J5, J6: PinSocket_1x04_P2.54mm_Vertical
J7: RJ14_Connfly_DS1133-S4_Horizontal

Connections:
DT: J6.2, J7.4
EXC_NEG: J1.2, J2.2, J3.2, J4.2, J5.2
EXC_POS: J1.1, J2.1, J3.1, J4.1, J5.1
GND: J6.1, J7.1
SCK: J6.3, J7.3
SIG_NEG: J2.3, J4.3, J5.4
SIG_POS: J1.3, J3.3, J5.3
VCC_3V3: J6.4, J7.2

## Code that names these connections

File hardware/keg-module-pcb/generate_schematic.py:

import re, uuid, pathlib

LIB_PATH = "/Applications/KiCad/KiCad.app/Contents/SharedSupport/symbols/Connector_Generic.kicad_sym"
OUT_DIR = pathlib.Path("/Users/arvid/projects/beeer-weight-proto/hardware/keg-module-pcb")
OUT_DIR.mkdir(parents=True, exist_ok=True)
PROJECT_NAME = "keg_sensor_module"
SCH_PATH = OUT_DIR / f"{PROJECT_NAME}.kicad_sch"

def extract_balanced(text, start_idx):
    depth = 0
    for i in range(start_idx, len(text)):
        c = text[i]
        if c == '(':
            depth += 1
        elif c == ')':
            depth -= 1
            if depth == 0:
                return text[start_idx:i+1]
    raise ValueError("unbalanced")

lib_text = open(LIB_PATH).read()

def get_symbol_block(name):
    idx = lib_text.index(f'(symbol "{name}"')
    block = extract_balanced(lib_text, idx)
    # qualify only the top-level symbol name (first occurrence at start of block)
    qualified = block.replace(f'(symbol "{name}"', f'(symbol "Connector_Generic:{name}"', 1)
    return qualified

conn3 = get_symbol_block("Conn_01x03")
conn4 = get_symbol_block("Conn_01x04")

def new_uuid():
    return str(uuid.uuid4())

ROOT_UUID = new_uuid()

# --- Component/net plan --------------------------------------------------
# J1-J4: half-bridge sensor terminals (3 pins: E+, E-, SIG)
# Diagonal corner pairing: J1(FL)+J3(BR) -> SIG_POS ; J2(FR)+J4(BL) -> SIG_NEG
# J5: HX711 header, load-cell side  -> pin1=E+ pin2=E- pin3=A+ pin4=A-
# J6: HX711 header, digital/power side -> pin1=GND pin2=DT pin3=SCK pin4=VCC
#     (verify against the specific module's silkscreen; order varies by vendor)
# J7: RJ11 jack -> pin1=GND(Black) pin2=VCC(Red) pin3=SCK(Green) pin4=DT(Yellow)
#     (must match the in-keezer hub's RJ11 pin convention for a straight cable)

PIN_DX = -5.08  # pin connection point x-offset from symbol origin (angle 0)
STUB = 2.54     # extra wire length from pin to label anchor
GRID = 1.27     # KiCad's default schematic connection grid (50 mil)

def snap(v):
    return round(round(v / GRID) * GRID, 2)

components = []  # each: dict(ref, lib, at, pins: [(num, net, label_side)])

def sensor(ref, x, y, corner):
    return dict(ref=ref, lib="Conn_01x03", at=(x, y), value=f"Sensor_{corner}",
                pins=[("1", "EXC_POS"), ("2", "EXC_NEG"), ("3", "SIG_POS" if corner in ("FL", "BR") else "SIG_NEG")],
                footprint="TerminalBlock:TerminalBlock_bornier-3_P5.08mm")

components.append(sensor("J1", 60, 30, "FL"))
components.append(sensor("J2", 60, 60, "FR"))
components.append(sensor("J3", 60, 90, "BR"))
components.append(sensor("J4", 60, 120, "BL"))

components.append(dict(ref="J5", lib="Conn_01x04", at=(150, 45), value="HX711_LoadCell_Side",
                        pins=[("1", "EXC_POS"), ("2", "EXC_NEG"), ("3", "SIG_POS"), ("4", "SIG_NEG")],
                        footprint="Connector_PinSocket_2.54mm:PinSocket_1x04_P2.54mm_Vertical"))

components.append(dict(ref="J6", lib="Conn_01x04", at=(150, 105), value="HX711_Digital_Side",
                        pins=[("1", "GND"), ("2", "DT"), ("3", "SCK"), ("4", "VCC_3V3")],
                        footprint="Connector_PinSocket_2.54mm:PinSocket_1x04_P2.54mm_Vertical"))

components.append(dict(ref="J7", lib="Conn_01x04", at=(240, 75), value="RJ11_to_Hub",
                        pins=[("1", "GND"), ("2", "VCC_3V3"), ("3", "SCK"), ("4", "DT")],
                        footprint=""))

# --- Build symbol instances + wires + labels ------------------------------

def indent(s, n):
    pad = "\t" * n
    return "\n".join(pad + line if line.strip() else line for line in s.split("\n"))

def prop(name, val, x, y, angle, hide=False, size=1.27):
    hide_s = "\n\t\t\t\t(hide yes)" if hide else ""
    return f'''\t\t(property "{name}" "{val}"
\t\t\t(at {x} {y} {angle})
\t\t\t(effects
\t\t\t\t(font
\t\t\t\t\t(size {size} {size})
\t\t\t\t){hide_s}
\t\t\t)
\t\t)'''

def sym_instance(ref, lib, x, y, value, footprint):
    u = new_uuid()
    pins_block = ""
    npins = 3 if lib == "Conn_01x03" else 4
    pin_uuids = []
    for i in range(1, npins + 1):
        pu = new_uuid()
        pin_uuids.append(pu)
        pins_block += f'\t\t(pin "{i}"\n\t\t\t(uuid "{pu}")\n\t\t)\n'
    ref_prop = prop("Reference", ref, x, y - 10, 0)
    val_prop = prop("Value", value, x, y + (10 if lib == "Conn_01x03" else 13), 0)
    fp_prop = prop("Footprint", footprint, x, y, 0, hide=True)
    ds_prop = prop("Datasheet", "~", x, y, 0, hide=True)
    block = f'''\t(symbol
\t\t(lib_id "Connector_Generic:{lib}")
\t\t(at {x} {y} 0)
\t\t(unit 1)
\t\t(exclude_from_sim no)
\t\t(in_bom yes)
\t\t(on_board yes)
\t\t(dnp no)
\t\t(uuid "{u}")
{ref_prop}
{val_prop}
{fp_prop}
{ds_prop}
{pins_block}\t\t(instances
\t\t\t(project "{PROJECT_NAME}"
\t\t\t\t(path "/{ROOT_UUID}"
\t\t\t\t\t(reference "{ref}")
\t\t\t\t\t(unit 1)
\t\t\t\t)
\t\t\t)
\t\t)
\t)'''
    return block

def wire_and_label(px, py, net, pin_dx_sign=-1):
    # stub extends further in -X from the pin connection point
    ex = px + pin_dx_sign * STUB
    ey = py
    wu = new_uuid()
    lu = new_uuid()
    wire = f'''\t(wire
\t\t(pts
\t\t\t(xy {px} {py}) (xy {ex} {ey})
\t\t)
\t\t(stroke
\t\t\t(width 0)
\t\t\t(type default)
\t\t)
\t\t(uuid "{wu}")
\t)'''
    label = f'''\t(label "{net}"
\t\t(at {ex} {ey} 0)
\t\t(effects
\t\t\t(font
\t\t\t\t(size 1.27 1.27)
\t\t\t)
\t\t\t(justify right)
\t\t)
\t\t(uuid "{lu}")
\t)'''
    return wire, label

symbol_blocks = []
wire_blocks = []
label_blocks = []
text_blocks = []

def add_text(msg, x, y, size=1.5):
    tu = new_uuid()
    text_blocks.append(f'''\t(text "{msg}"
\t\t(at {x} {y} 0)
\t\t(effects
\t\t\t(font
\t\t\t\t(size {size} {size})
\t\t\t)
\t\t)
\t\t(uuid "{tu}")
\t)''')

for c in components:
    x, y = snap(c["at"][0]), snap(c["at"][1])
    symbol_blocks.append(sym_instance(c["ref"], c["lib"], x, y, c["value"], c["footprint"]))
    pin_dy_start = 2.54  # pin 1 offset from symbol origin, per library def
    for num, net in c["pins"]:
        dy = pin_dy_start - (int(num) - 1) * 2.54
        px = x + PIN_DX
        # KiCad negates the symbol-local Y axis when placing at rotation 0
        # (lib editor is Y-up, schematic sheet is Y-down) - confirmed via ERC.
        py = y - dy
        w, l = wire_and_label(px, py, net)
        wire_blocks.append(w)
        label_blocks.append(l)

# Documentation text annotations (non-electrical)
add_text("Keg Sensor Module - carrier for HX711 breakout + 4x half-bridge sensors + RJ11 to hub", 20, 10, 2)
add_text("J1=FL J2=FR J3=BR J4=BL corner sensors.\\nDiagonal pairing: J1+J3 -> SIG_POS, J2+J4 -> SIG_NEG.\\nVerify against kit's wiring diagram - swap if reading is inverted/flat.", 20, 145, 1.27)
add_text("J6 pin order (GND,DT,SCK,VCC) is a common HX711 module layout -\\nCONFIRM against your specific module's silkscreen before wiring/routing.", 130, 130, 1.27)
add_text("J7 = RJ11 jack to in-keezer hub.\\nPin1=GND(Black) Pin2=VCC(Red) Pin3=SCK(Green) Pin4=DT(Yellow).\\nMust match hub-side RJ11 pin convention (hub-wiring.md) for a straight-through cable.\\nFootprint intentionally left blank - assign to match your exact RJ11 jack part.", 220, 40, 1.27)

sch = f'''(kicad_sch
\t(version 20250114)
\t(generator "eeschema")
\t(generator_version "9.0")
\t(uuid "{ROOT_UUID}")
\t(paper "A3")
\t(title_block
\t\t(title "Keg Sensor Module")
\t\t(comment 1 "HX711 carrier + 4x half-bridge sensor terminals + RJ11 to hub")
\t)
\t(lib_symbols
{indent(conn3, 2)}
{indent(conn4, 2)}
\t)
{chr(10).join(symbol_blocks)}
{chr(10).join(wire_blocks)}
{chr(10).join(label_blocks)}
{chr(10).join(text_blocks)}
\t(sheet_instances
\t\t(path "/"
\t\t\t(page "1")
\t\t)
\t)
\t(embedded_fonts no)
)
'''

SCH_PATH.write_text(sch)
print("wrote", SCH_PATH)
